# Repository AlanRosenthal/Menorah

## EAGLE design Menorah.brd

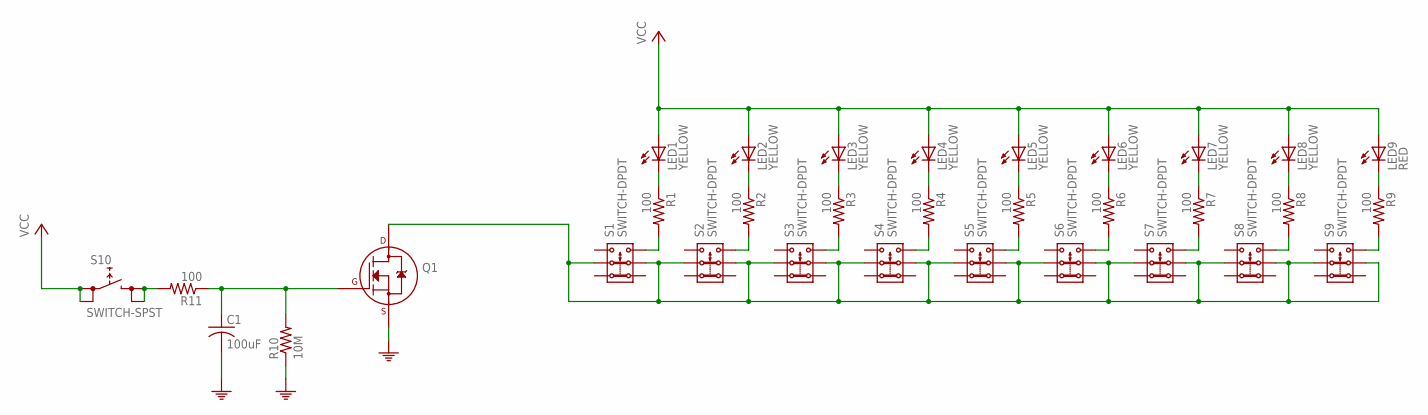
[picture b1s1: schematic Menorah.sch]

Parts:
C1: 100uF; C1206; DIGIKEY 490-4539-1-ND
LED1, LED2, LED3, LED4, LED5, LED6, LED7, LED8: YELLOW; CHIPLED_0805; DIGIKEY 475-2560-1-ND
LED9: RED; CHIPLED_0805; DIGIKEY 475-1415-1-ND
Q1: 2N7002A_SOT23; SOT-23
R1, R2, R3, R4, R5, R6, R7, R8, R9, R11: 100; R0805; DIGIKEY 1276-5508-1-ND
R10: 10M; R0805; DIGIKEY 1276-5617-1-ND
S1, S2, S3, S4, S5, S6, S7, S8, S9: SWITCH-DPDT; JS202011SCQN; DIGIKEY 401-2002-1-ND
S10: SWITCH-SPST; KS-01Q-01; DIGIKEY EG4791-ND

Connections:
unnamed: LED1.C, R1.1
unnamed: LED2.C, R2.1
unnamed: LED3.C, R3.1
unnamed: LED4.C, R4.1
unnamed: LED5.C, R5.1
unnamed: LED6.C, R6.1
unnamed: LED7.C, R7.1
unnamed: LED8.C, R8.1
unnamed: LED9.C, R9.1
unnamed: R1.2, S1.3
unnamed: R2.2, S2.3
unnamed: R3.2, S3.3
unnamed: R4.2, S4.3
unnamed: R5.2, S5.3
unnamed: R6.2, S6.3
unnamed: R7.2, S7.3
unnamed: R8.2, S8.3
unnamed: R9.2, S9.3
unnamed: R11.2, S10.2 (1), S10.4 (1)
unnamed: Q1.3 (D), S1.2, S1.5, S2.2, S2.5, S3.2, S3.5, S4.2, S4.5, S5.2, S5.5, S6.2, S6.5, S7.2, S7.5, S8.2, S8.5, S9.2, S9.5
unnamed: C1.1, Q1.1 (G), R10.2, R11.1
PE: C1.2, Q1.2 (S), R10.1
VCC: LED1.A, LED2.A, LED3.A, LED4.A, LED5.A, LED6.A, LED7.A, LED8.A, LED9.A, S10.1 (0), S10.3 (0)

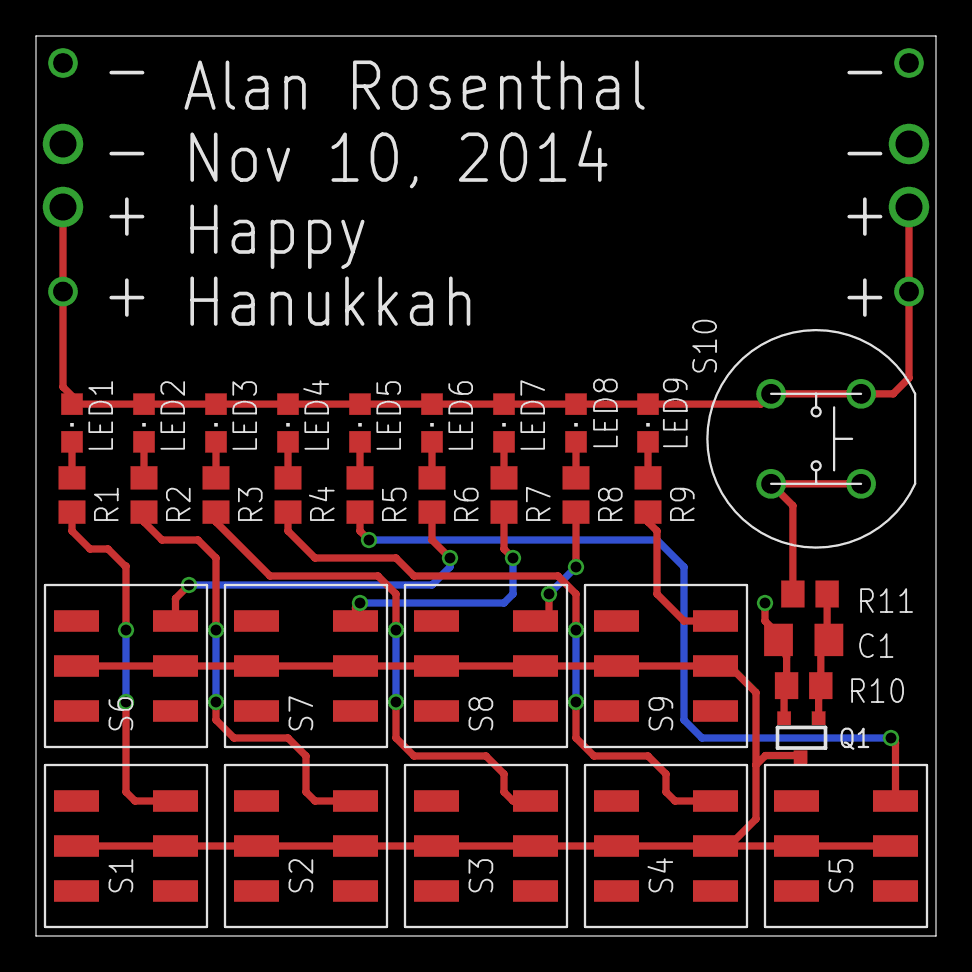
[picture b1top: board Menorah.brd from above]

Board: 2 copper layers, 50.0 x 50.0 mm, 32 parts (0 on the bottom side), 23 nets.

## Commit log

2014-11-09 inital commit
2014-11-09 design finished
2014-11-09 digikey part numbers added
2014-11-09 replaced cr2032
2014-11-09 replaced spst switch
2014-11-09 replaced dpdt switch
2014-11-09 dru and cam from seeed
2014-11-11 changed circircuit, updated pcb
2014-11-11 updated cam file
2014-11-11 updated cam to put files in cam dir
2014-11-11 generated cam files
2014-11-11 zip file
